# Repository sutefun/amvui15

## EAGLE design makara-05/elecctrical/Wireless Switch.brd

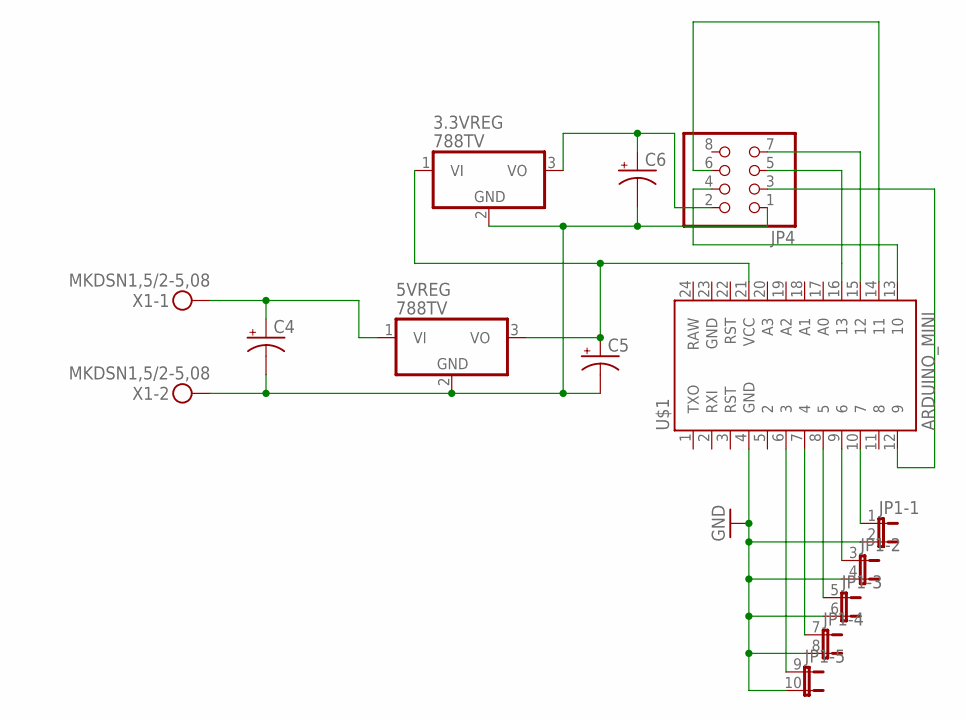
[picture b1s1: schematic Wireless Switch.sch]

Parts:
3.3VREG, 5VREG: 788TV; TO220V
C4, C5: CPOL-USE3.5-8; E3,5-8
C6: CPOL-USE2.5-6; E2,5-6
JP1: JP5QE; JP5Q
JP4: PINHD-2X4; 2X04
U$1: ARDUINO_MINI
X1: MKDSN1,5/2-5,08

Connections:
GND: JP1.2, JP1.4 (2), JP1.6 (2), JP1.8 (2), JP1.10 (2), U$1.4 (GND)
unnamed: 5VREG.1 (VI), C4.+, X1.1
unnamed: 3.3VREG.2 (GND), 5VREG.2 (GND), C4.-, C5.-, C6.-, JP4.1, X1.2
unnamed: 3.3VREG.1 (VI), 5VREG.3 (VO), C5.+, U$1.21 (VCC)
unnamed: JP1.9 (1), U$1.6 (3)
unnamed: JP1.7 (1), U$1.7 (4)
unnamed: JP1.5 (1), U$1.8 (5)
unnamed: JP1.3 (1), U$1.9 (6)
unnamed: JP1.1, U$1.10 (7)
unnamed: 3.3VREG.3 (VO), C6.+, JP4.2
unnamed: JP4.6, U$1.14 (11)
unnamed: JP4.4, U$1.13 (10)
unnamed: JP4.7, U$1.15 (12)
unnamed: JP4.5, U$1.16 (13)
unnamed: JP4.3, U$1.12 (9)

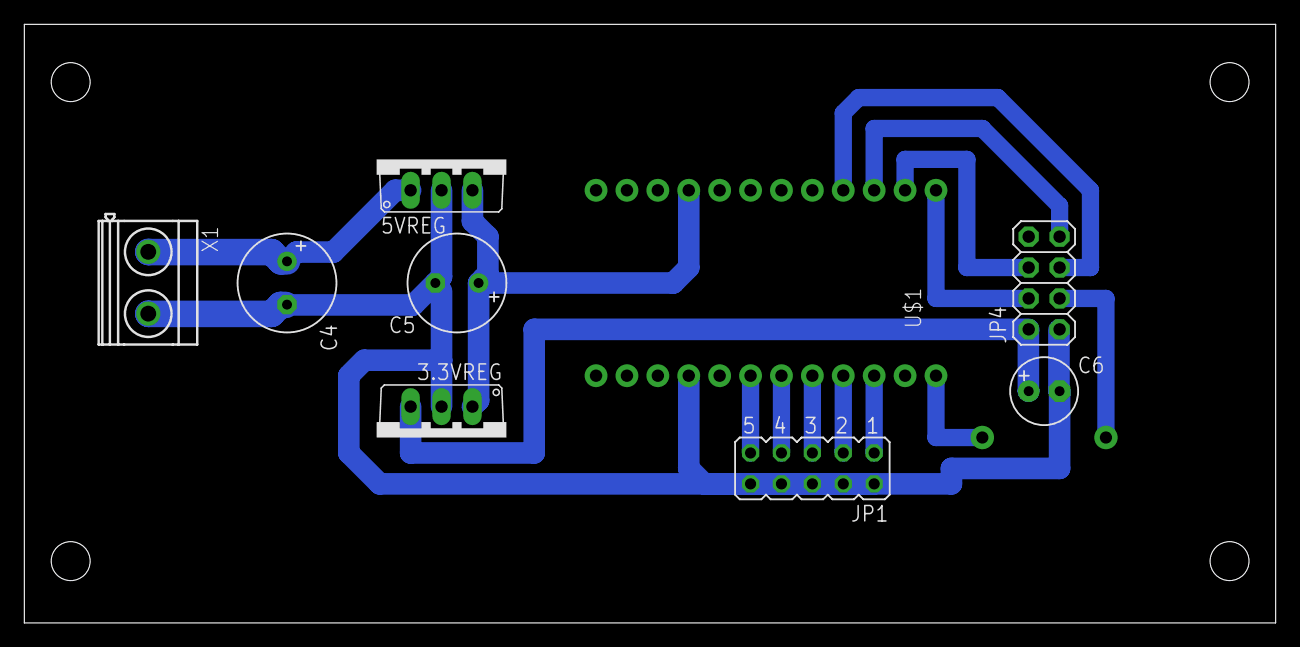
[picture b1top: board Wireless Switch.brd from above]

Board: 2 copper layers, 102.8 x 49.2 mm, 9 parts (0 on the bottom side), 15 nets.

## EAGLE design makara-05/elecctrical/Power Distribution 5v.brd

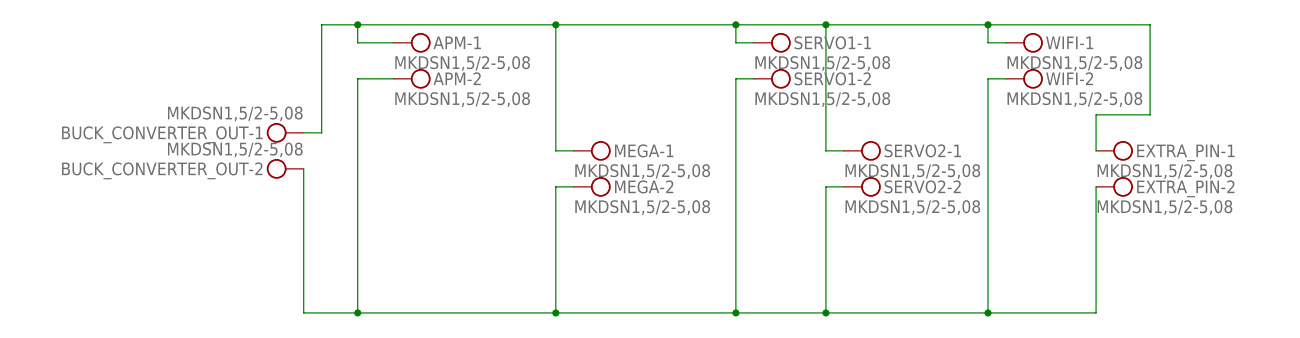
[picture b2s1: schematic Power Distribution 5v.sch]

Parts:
APM: MKDSN1,5/2-5,08
BUCK_CONVERTER_OUT: MKDSN1,5/2-5,08
EXTRA_PIN: MKDSN1,5/2-5,08
MEGA: MKDSN1,5/2-5,08
SERVO1, SERVO2: MKDSN1,5/2-5,08
WIFI: MKDSN1,5/2-5,08

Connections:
unnamed: APM.1, BUCK_CONVERTER_OUT.1, EXTRA_PIN.1, MEGA.1, SERVO1.1, SERVO2.1, WIFI.1
unnamed: APM.2, BUCK_CONVERTER_OUT.2, EXTRA_PIN.2, MEGA.2, SERVO1.2, SERVO2.2, WIFI.2

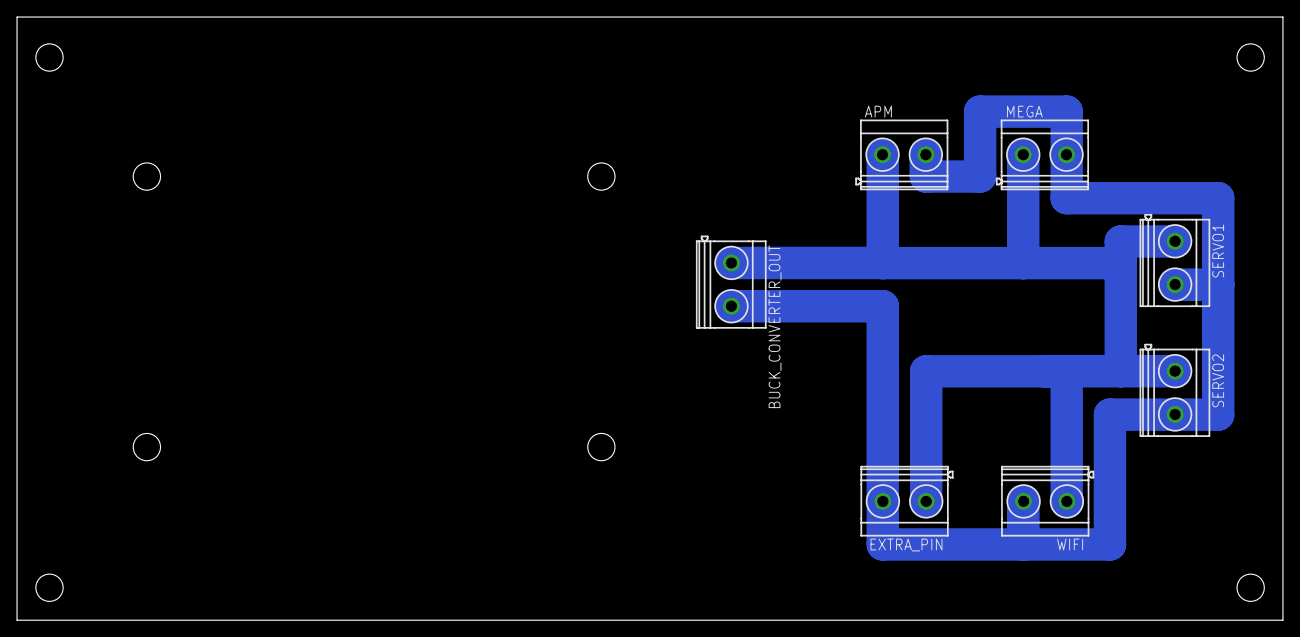
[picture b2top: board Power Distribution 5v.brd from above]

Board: 2 copper layers, 148.6 x 70.8 mm, 7 parts (0 on the bottom side), 2 nets.

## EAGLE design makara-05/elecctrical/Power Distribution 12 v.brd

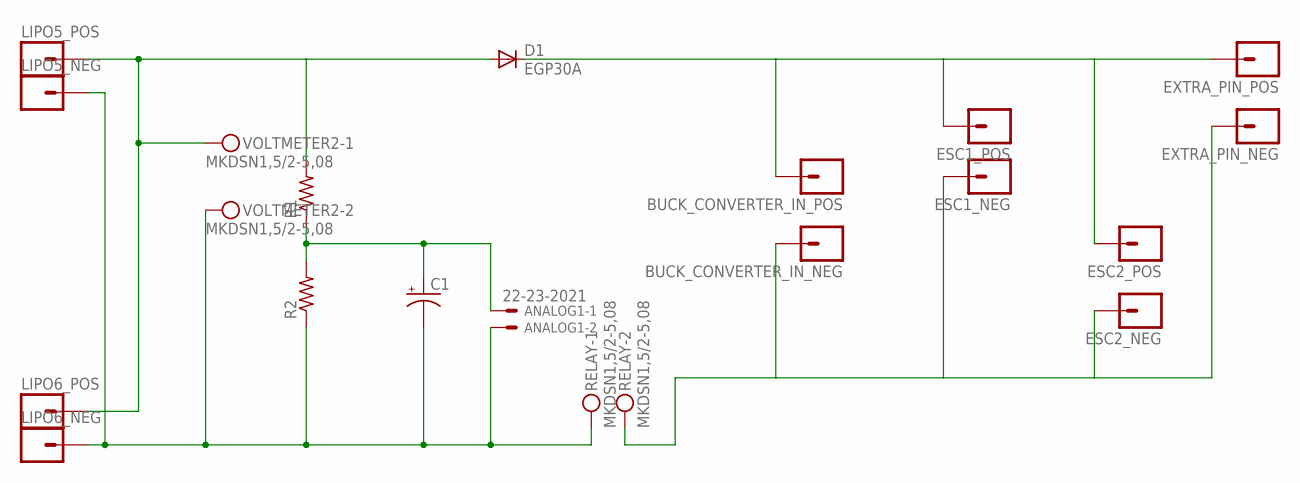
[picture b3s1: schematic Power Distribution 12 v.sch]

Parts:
ANALOG1: 22-23-2021
BUCK_CONVERTER_IN_NEG: M01PTH_2MM; 1X01_2MM
BUCK_CONVERTER_IN_POS: M01PTH_2MM; 1X01_2MM
C1: CPOL-USE2-5; E2-5
D1: EGP30A; DO201-15
ESC1_NEG, ESC1_POS, ESC2_NEG, ESC2_POS: M01PTH_2MM; 1X01_2MM
EXTRA_PIN_NEG: M01PTH_2MM; 1X01_2MM
EXTRA_PIN_POS: M01PTH_2MM; 1X01_2MM
LIPO5_NEG, LIPO5_POS, LIPO6_NEG, LIPO6_POS: M01PTH_2MM; 1X01_2MM
R1, R2: R-US_0207/10; 0207/10
RELAY: MKDSN1,5/2-5,08
VOLTMETER2: MKDSN1,5/2-5,08

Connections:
unnamed: D1.A, LIPO5_POS.1, LIPO6_POS.1, R1.2, VOLTMETER2.1
unnamed: ANALOG1.1, C1.+, R1.1, R2.2
unnamed: ANALOG1.2, C1.-, LIPO5_NEG.1, LIPO6_NEG.1, R2.1, RELAY.1, VOLTMETER2.2
unnamed: BUCK_CONVERTER_IN_POS.1, D1.C, ESC1_POS.1, ESC2_POS.1, EXTRA_PIN_POS.1
unnamed: BUCK_CONVERTER_IN_NEG.1, ESC1_NEG.1, ESC2_NEG.1, EXTRA_PIN_NEG.1, RELAY.2

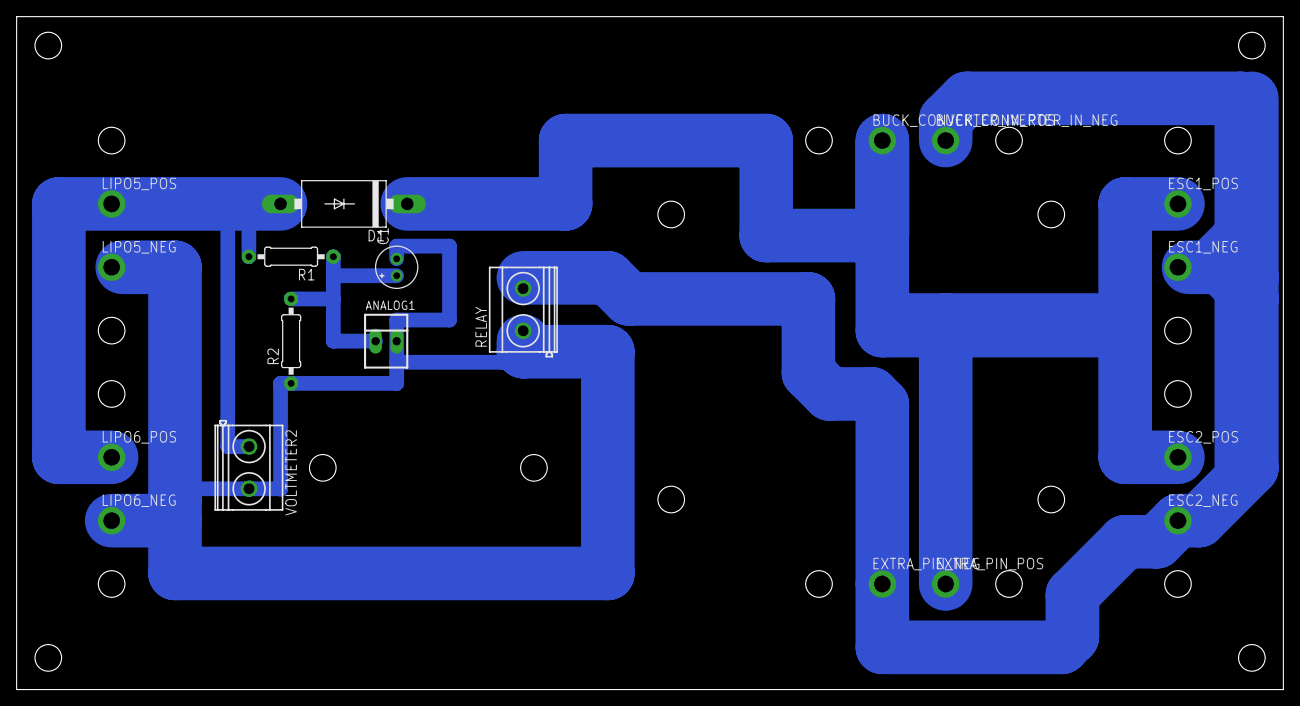
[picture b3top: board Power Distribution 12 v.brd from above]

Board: 2 copper layers, 152.4 x 81.0 mm, 19 parts (0 on the bottom side), 5 nets.

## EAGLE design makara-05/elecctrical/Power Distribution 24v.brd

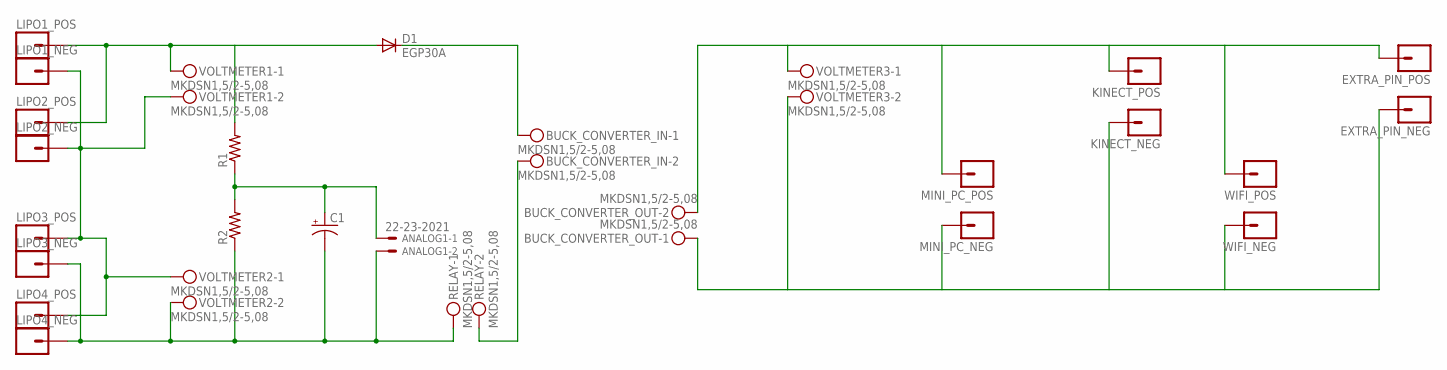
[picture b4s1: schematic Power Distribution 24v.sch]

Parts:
ANALOG1: 22-23-2021
BUCK_CONVERTER_IN: MKDSN1,5/2-5,08
BUCK_CONVERTER_OUT: MKDSN1,5/2-5,08
C1: CPOL-USE2-5; E2-5
D1: EGP30A; DO201-15
EXTRA_PIN_NEG: M01PTH_2MM; 1X01_2MM
EXTRA_PIN_POS: M01PTH_2MM; 1X01_2MM
KINECT_NEG: M01PTH_2MM; 1X01_2MM
KINECT_POS: M01PTH_2MM; 1X01_2MM
LIPO1_NEG, LIPO1_POS, LIPO2_NEG, LIPO2_POS, LIPO3_NEG, LIPO3_POS, LIPO4_NEG, LIPO4_POS: M01PTH_2MM; 1X01_2MM
MINI_PC_NEG: M01PTH_2MM; 1X01_2MM
MINI_PC_POS: M01PTH_2MM; 1X01_2MM
R1, R2: R-US_0207/10; 0207/10
RELAY: MKDSN1,5/2-5,08
VOLTMETER1, VOLTMETER2, VOLTMETER3: MKDSN1,5/2-5,08
WIFI_NEG: M01PTH_2MM; 1X01_2MM
WIFI_POS: M01PTH_2MM; 1X01_2MM

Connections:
unnamed: D1.A, LIPO1_POS.1, LIPO2_POS.1, R1.2, VOLTMETER1.1
unnamed: ANALOG1.1, C1.+, R1.1, R2.2
unnamed: LIPO1_NEG.1, LIPO2_NEG.1, LIPO3_POS.1, LIPO4_POS.1, VOLTMETER1.2, VOLTMETER2.1
unnamed: BUCK_CONVERTER_IN.1, D1.C
unnamed: ANALOG1.2, C1.-, LIPO3_NEG.1, LIPO4_NEG.1, R2.1, RELAY.1, VOLTMETER2.2
unnamed: BUCK_CONVERTER_IN.2, RELAY.2
unnamed: BUCK_CONVERTER_OUT.2, EXTRA_PIN_POS.1, KINECT_POS.1, MINI_PC_POS.1, VOLTMETER3.1, WIFI_POS.1
unnamed: BUCK_CONVERTER_OUT.1, EXTRA_PIN_NEG.1, KINECT_NEG.1, MINI_PC_NEG.1, VOLTMETER3.2, WIFI_NEG.1

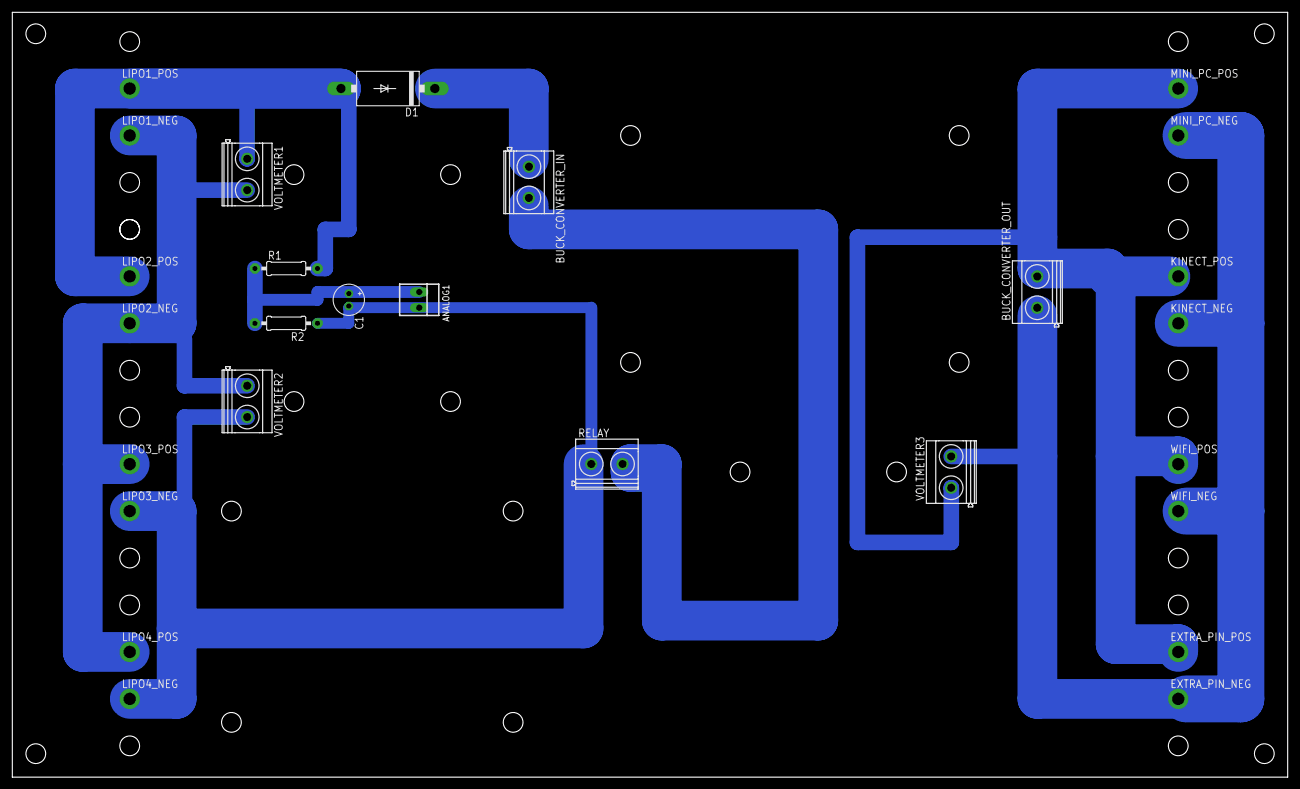
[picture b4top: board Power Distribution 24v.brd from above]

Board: 2 copper layers, 207.0 x 124.1 mm, 27 parts (0 on the bottom side), 8 nets.

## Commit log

2015-08-28 eelectrical hardware
2015-08-28 veentilator pict

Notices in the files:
parts and their libraries:
SparkFun-Connectors: Licensing: Creative Commons ShareAlike 4.0 International - https://creativecommons.org/licenses/by-sa/4.0
